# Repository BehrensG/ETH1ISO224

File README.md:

<h1>ETH1ISO224</h1>

ETH1ISO224 is a one-channel data acquisition card based on the ISO224 chip. The communication with a PC is over Ethernet. The card supports LAN eXtensions for Instrumentation (LXI) and RAW TCP and UDP connections.

> [!CAUTION]
> This design is still in verification phase. The device requires a calibration and validation to be done.

<h2>DESCRIPTION</h2>

<h3>Device Design</h3>

Key features of the design include:

<ul>
    <li><b>Dimensions</b>: 100 x 45 mm</li>
    <li><b>Power Supply</b>: Operates on a voltage range from 6.5 to 36 VDC (recommended 24 VDC) and includes reverse voltage protection.</li>
    <li><b>Isolation</b>: The ISO224 chip with TBA 1-0513HI provides isolation protection for the rest of the circuit.</li>
    <li><b>MCU</b>: The STM32H743VITx was selected because of its large internal FLASH and RAM memory, support for Ethernet, and internal 16-bit ADC.</li>
    <li><b>ADC</b>: Internal 16 bit ADC, configured in differential mode.</li>
    <li><b>Software</b>: FreeRTOS with lwip and SCPI parser library.</li>
</ul>

<p align="center">3D model rendition for PCB V1.2.</p>
<p align="center"></img></p>

<p align="center">Below are the images for the PCB V1.0.</p>

<p align="center"></img></p>
<p align="center"></img></p>
<p align="center"></img></p>

<h3>Input voltage</h3>

The PCB was designed for max bipolar 1000V DC measurements. It will divide the input voltage by 100. The user can use 1776-C68xx or SMD resistors to create the voltage divider.

> [!CAUTION]
> The PCB is still in verification. There are no guarantees that it can handle 1000 VDC safely.

<h2>Ethernet connection</h2>

The PCB uses Ethernet to communicate with the PC. The features are :

<h3>LAN eXtensions for Instrumentation (LXI)</h3>

LAN eXtensions for Instrumentation (LXI) is a standard for connecting and controlling test and measurement instruments via Ethernet. It allows for easy integration, remote access, and simplified configuration, enhancing the flexibility and scalability of automated test systems.

> [!WARNING]  
> This device does not guarantee full compliance with the LXI standard. The implementation was based on available documentation and observations of an LXI-compliant device.

> [!TIP]
> To use the LXI features the user needs to use a VISA API. In the examples below, the R&S VISA Tools where uses. 

<h4><p align="center">Device autodetect with multicast DNS (mDNS).</p></h4>
<hr>
<p align="center"></img></p>

<h4><p align="center">Support for High Speed LAN Instrument Protocol (HiSLIP).</p></h4>
<hr>
<p align="center"></img></p>

<h4><p align="center">Web interface</p></h4>
<hr>
The device website provides the ability to obtain device information, make measurements, and configure the device. Additionally, it offers a manual with all SCPI commands.

> [!WARNING]
> The website was tested only with Google Chrome  Browser.

<h5><p align="center">Device Home Page</p></h5>
<hr>
<p align="center"></img></p>

<h5><p align="center">Device Network Setup</p></h5>
<hr>
<p align="center"></img></p>

<h5><p align="center">Device Control</p></h5>
<hr>
<p align="center"></img></p>

<h5><p align="center">Device Help</p></h5>
<hr>
<p align="center"></img></p>

<h5><p align="center">Device Service</p></h5>
<hr>
<p align="center"></img></p>

<h3>RAW TCP</h3>
The user can connect to the device directly over the TCP 5025 port.

<h5><p align="center">Using netcat</p></h5>
<hr>
<p align="center"></img></p>

<h5><p align="center">Using putty</p></h5>
<hr>
<p align="center"></img></p>

<h3>RAW UDP</h3>
The user can connect to the device directly via UDP port 5025. Over UDP, there is a very limited set of SCPI commands available for measurement readout.

> [!WARNING]
> The RAW UDP connection is not part of the LXI standard, it is device specific.

<h5><p align="center">Using netcat</p></h5>
<hr>
<p align="center"></img></p>

<h2>Links</h2>

<ul>
    <li><a href="https://www.ti.com/product/ISO224" target="_blank">ISO224</a></li>
    <li><a href="https://www.lxistandard.org/" target="_blank">LAN eXtensions for Instrumentation</a></li>
    <li><a href="https://www.ivifoundation.org/specifications/default.html" target="_blank">High Speed LAN Instrument Protocol (HiSLIP)</a></li>
    <li><a href="https://en.wikipedia.org/wiki/Virtual_instrument_software_architecture" target="_blank">Virtual instrument software architecture (VISA)</a></li>
    <li><a href="https://www.rohde-schwarz.com/us/driver-pages/remote-control/3-visa-and-tools_231388.html" target="_blank">R&S VISA</a></li>
    <li><a href="https://github.com/j123b567/scpi-parser" target="_blank">SCPI Parser</a></li>
   <li><a href="https://github.com/mpaland/printf" target="_blank">A printf / sprintf Implementation for Embedded Systems</a></li>
</ul>

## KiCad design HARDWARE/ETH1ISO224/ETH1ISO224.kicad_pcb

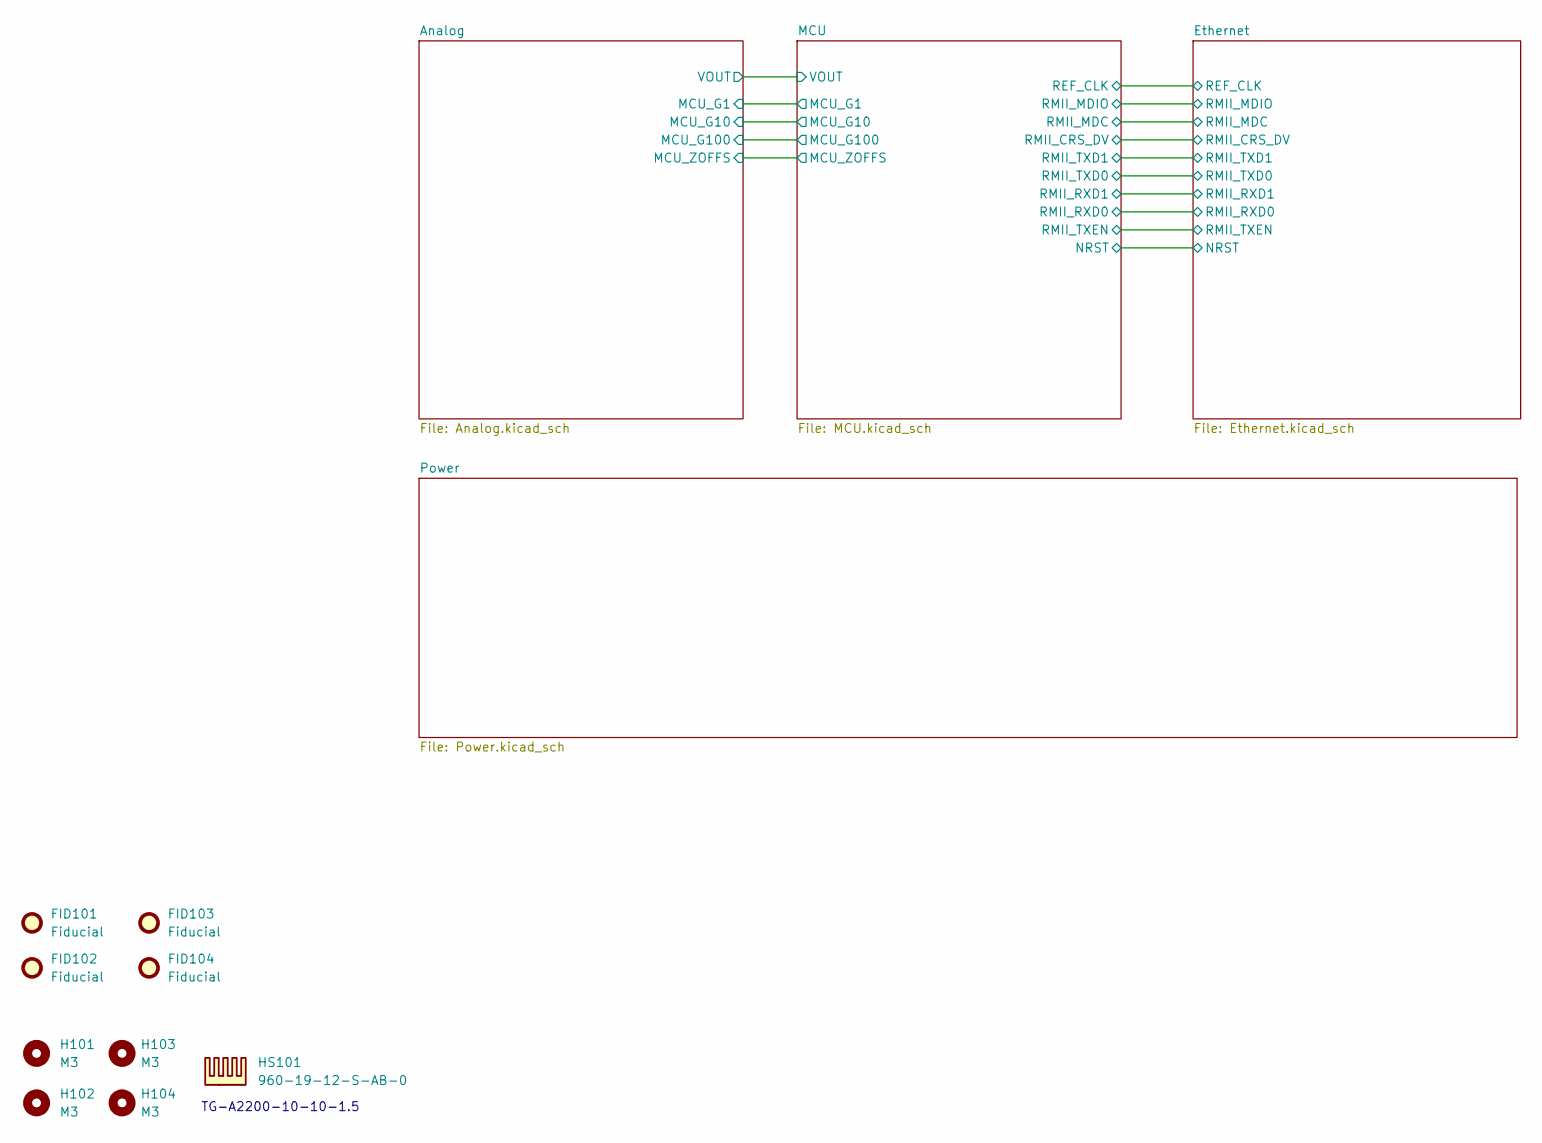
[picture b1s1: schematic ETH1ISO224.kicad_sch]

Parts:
FID101, FID102, FID103, FID104: Fiducial; Fiducial_1.5mm_Mask3mm
H101, H102: M3; MountingHole_3.2mm_M3_DIN965
H103, H104: M3; MountingHole_3.2mm_M3_DIN965_Pad
HS101: 960-19-12-S-AB-0

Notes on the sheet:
TG-A2200-10-10-1.5

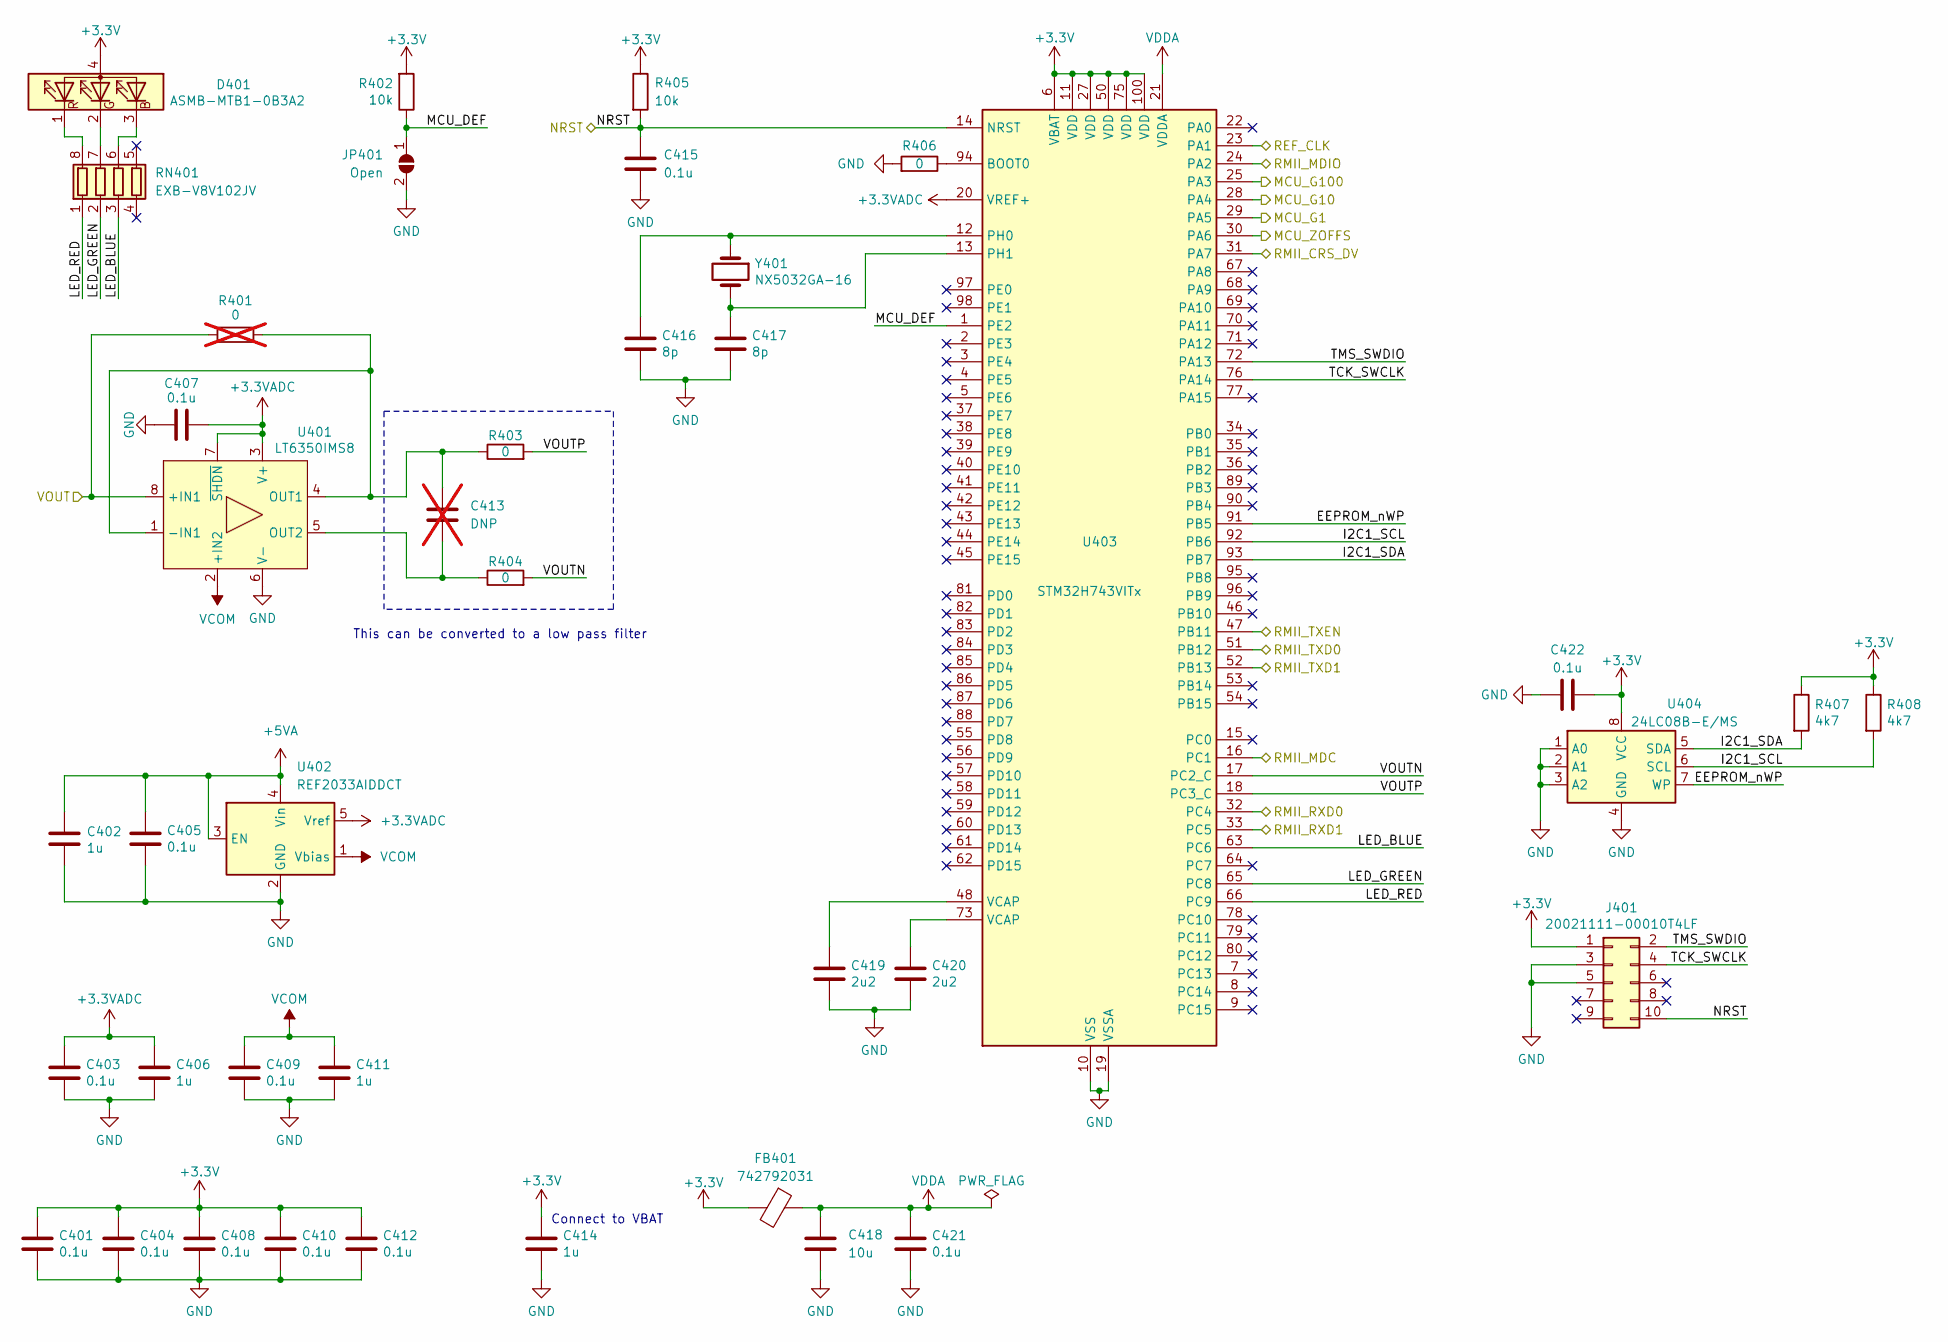
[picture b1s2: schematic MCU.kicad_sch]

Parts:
C401, C403, C404, C405, C407, C408, C409, C410, C412, C415, C421, C422: 0.1u; C_0603_1608Metric_Pad1.08x0.95mm_HandSolder
C402, C406, C411, C414: 1u; C_0603_1608Metric_Pad1.08x0.95mm_HandSolder
C413: DNP; C_0603_1608Metric_Pad1.08x0.95mm_HandSolder; not fitted
C416, C417: 8p; C_0603_1608Metric_Pad1.08x0.95mm_HandSolder
C418: 10u; C_0603_1608Metric_Pad1.08x0.95mm_HandSolder
C419, C420: 2u2; C_0603_1608Metric_Pad1.08x0.95mm_HandSolder
D401: ASMB-MTB1-0B3A2; LED_Avago_PLCC4_3.2x2.8mm_CW
FB401: 742792031; L_0805_2012Metric_Pad1.05x1.20mm_HandSolder
J401: 20021111-00010T4LF; PinHeader_2x05_P1.27mm_Vertical
JP401: Open; SolderJumper-2_P1.3mm_Open_Pad1.0x1.5mm
R401: 0; R_0603_1608Metric_Pad0.98x0.95mm_HandSolder; not fitted
R402, R405: 10k; R_0603_1608Metric_Pad0.98x0.95mm_HandSolder
R403, R404, R406: 0; R_0603_1608Metric_Pad0.98x0.95mm_HandSolder
R407, R408: 4k7; R_0603_1608Metric_Pad0.98x0.95mm_HandSolder
RN401: EXB-V8V102JV; R_Array_Concave_4x0603
U401: LT6350IMS8; MSOP-8_3x3mm_P0.65mm
U402: REF2033AIDDCT; SOT-23-5
U403: STM32H743VITx; LQFP-100_14x14mm_P0.5mm
U404: 24LC08B-E/MS; MSOP-8_3x3mm_P0.65mm
Y401: NX5032GA-16; NX5032GA

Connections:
+3.3V: C401.1, C404.1, C408.1, C410.1, C412.1, C414.1, C422.2, D401.4 (A), FB401.2, J401.1, R402.2, R405.1, R407.1, R408.1, U403.6 (VBAT), U403.11 (VDD), U403.27 (VDD), U403.50 (VDD), U403.75 (VDD), U403.100 (VDD), U404.8 (VCC); also elsewhere on the board
+3.3VADC: C403.1, C406.1, C407.1, U401.3 (V+), U401.7 (~SHDN), U402.5 (Vref), U403.20 (VREF+)
+5VA: C402.1, C405.1, U402.3 (EN), U402.4 (Vin); also elsewhere on the board
/Analog/MCU_G1: U403.29 (PA5); also elsewhere on the board
/Analog/MCU_G10: U403.28 (PA4); also elsewhere on the board
/Analog/MCU_G100: U403.25 (PA3); also elsewhere on the board
/Analog/MCU_ZOFFS: U403.30 (PA6); also elsewhere on the board
/Analog/VOUT: R401.1, U401.8 (+IN1); also elsewhere on the board
/Ethernet/REF_CLK: U403.23 (PA1); also elsewhere on the board
/Ethernet/RMII_CRS_DV: U403.31 (PA7); also elsewhere on the board
/Ethernet/RMII_MDC: U403.16 (PC1); also elsewhere on the board
/Ethernet/RMII_MDIO: U403.24 (PA2); also elsewhere on the board
/Ethernet/RMII_RXD0: U403.32 (PC4); also elsewhere on the board
/Ethernet/RMII_RXD1: U403.33 (PC5); also elsewhere on the board
/Ethernet/RMII_TXD0: U403.51 (PB12); also elsewhere on the board
/Ethernet/RMII_TXD1: U403.52 (PB13); also elsewhere on the board
/Ethernet/RMII_TXEN: U403.47 (PB11); also elsewhere on the board
/MCU/EEPROM_nWP: U403.91 (PB5), U404.7 (WP)
/MCU/I2C1_SCL: R408.2, U403.92 (PB6), U404.6 (SCL)
/MCU/I2C1_SDA: R407.2, U403.93 (PB7), U404.5 (SDA)
/MCU/LED_BLUE: RN401.3 (R3.1), U403.63 (PC6)
/MCU/LED_GREEN: RN401.2 (R2.1), U403.65 (PC8)
/MCU/LED_RED: RN401.1 (R1.1), U403.66 (PC9)
/MCU/MCU_DEF: JP401.1 (A), R402.1, U403.1 (PE2)
/MCU/NRST: C415.1, J401.10, R405.2, U403.14 (NRST); also elsewhere on the board
/MCU/TCK_SWCLK: J401.4, U403.76 (PA14)
/MCU/TMS_SWDIO: J401.2, U403.72 (PA13)
/MCU/VOUTN: R404.2, U403.17 (PC2_C)
/MCU/VOUTP: R403.2, U403.18 (PC3_C)
GND: C401.2, C402.2, C403.2, C404.2, C405.2, C406.2, C407.2, C408.2, C409.2, C410.2, C411.2, C412.2, C414.2, C415.2, C416.2, C417.2, C418.2, C419.2, C420.2, C421.2, C422.1, J401.3, J401.5, JP401.2 (B), R406.2, U401.6 (V-), U402.2 (GND), U403.10 (VSS), U403.19 (VSSA), U403.26 (VSS), U403.49 (VSS), U403.74 (VSS), U403.99 (VSS), U404.1 (A0), U404.2 (A1), U404.3 (A2), U404.4 (GND); also elsewhere on the board
unnamed: C419.1, U403.48 (VCAP)
unnamed: C420.1, U403.73 (VCAP)
unnamed: D401.3 (BK), RN401.6 (R3.2)
unnamed: D401.2 (GK), RN401.7 (R2.2)
unnamed: D401.1 (RK), RN401.8 (R1.2)
unnamed: C413.1, R401.2, R403.1, U401.1 (-IN1), U401.4 (OUT1)
unnamed: C413.2, R404.1, U401.5 (OUT2)
unnamed: R406.1, U403.94 (BOOT0)
unnamed: C416.1, U403.12 (PH0), Y401.1
unnamed: C417.1, U403.13 (PH1), Y401.2
VCOM: C409.1, C411.1, U401.2 (+IN2), U402.1 (Vbias); also elsewhere on the board
VDDA: C418.1, C421.1, FB401.1, U403.21 (VDDA)

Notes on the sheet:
This can be converted to a low pass filter
Connect to VBAT

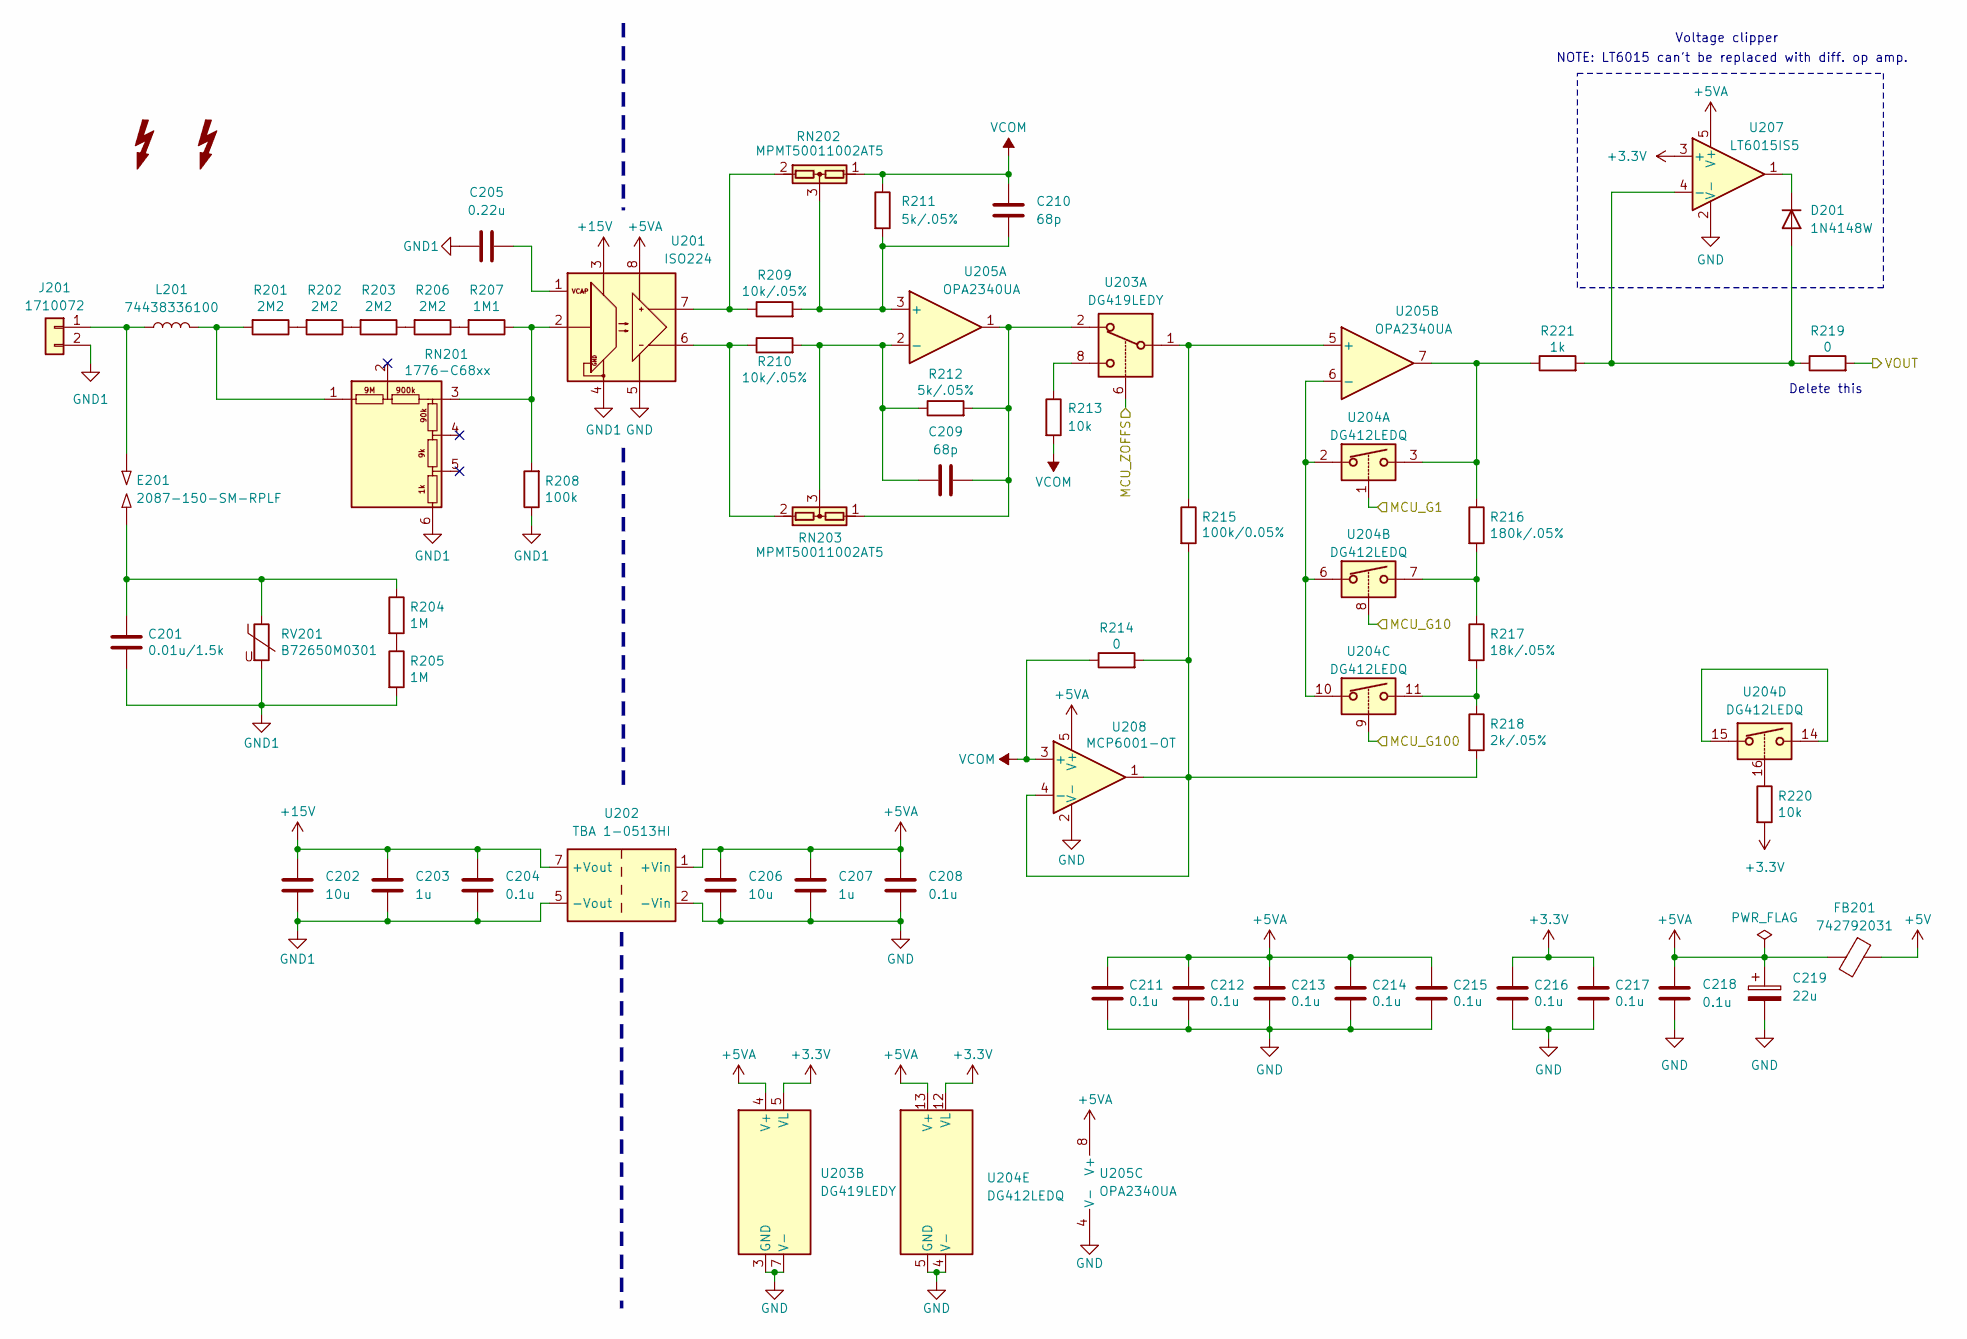
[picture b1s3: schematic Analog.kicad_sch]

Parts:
C201: 0.01u/1.5k; C_1206_3216Metric_Pad1.33x1.80mm_HandSolder
C202, C206: 10u; C_1206_3216Metric_Pad1.33x1.80mm_HandSolder
C203, C207: 1u; C_0603_1608Metric_Pad1.08x0.95mm_HandSolder
C204, C208, C211, C212, C213, C214, C215, C216, C217, C218: 0.1u; C_0603_1608Metric_Pad1.08x0.95mm_HandSolder
C205: 0.22u; C_0603_1608Metric_Pad1.08x0.95mm_HandSolder
C209, C210: 68p; C_0603_1608Metric_Pad1.08x0.95mm_HandSolder
C219: 22u; CP_EIA-3528-21_Kemet-B_Pad1.50x2.35mm_HandSolder
D201: 1N4148W; D_SOD-123
E201: 2087-150-SM-RPLF; 2087
FB201: 742792031; L_0805_2012Metric_Pad1.05x1.20mm_HandSolder
J201: 1710072
L201: 74438336100; L_Wuerth_MAPI-3015
R201, R202, R203, R206: 2M2; R_1206_3216Metric_Pad1.30x1.75mm_HandSolder
R204, R205: 1M; R_1206_3216Metric_Pad1.30x1.75mm_HandSolder
R207: 1M1; R_1206_3216Metric_Pad1.30x1.75mm_HandSolder
R208: 100k; R_1206_3216Metric_Pad1.30x1.75mm_HandSolder
R209, R210: 10k/.05%; R_0603_1608Metric_Pad0.98x0.95mm_HandSolder
R211, R212: 5k/.05%; R_0603_1608Metric_Pad0.98x0.95mm_HandSolder
R213, R220: 10k; R_0603_1608Metric_Pad0.98x0.95mm_HandSolder
R214, R219: 0; R_0603_1608Metric_Pad0.98x0.95mm_HandSolder
R215: 100k/0.05%; R_0603_1608Metric_Pad0.98x0.95mm_HandSolder
R216: 180k/.05%; R_0603_1608Metric_Pad0.98x0.95mm_HandSolder
R217: 18k/.05%; R_0603_1608Metric_Pad0.98x0.95mm_HandSolder
R218: 2k/.05%; R_0603_1608Metric_Pad0.98x0.95mm_HandSolder
R221: 1k; R_0603_1608Metric_Pad0.98x0.95mm_HandSolder
RN201: 1776-C68xx
RN202, RN203: MPMT50011002AT5; SOT-23
RV201: B72650M0301; Varistor_Panasonic_VF
SYM201, SYM202: SYM_Flash_Small; Symbol_Attention_Triangle_8x7mm_Copper
U201: ISO224; SSO-8_6.8x5.9mm_P1.27mm_Clearance8mm
U202: TBA 1-0513HI; TBA 1HI
U203: DG419LEDY; SOIC-8_3.9x4.9mm_P1.27mm
U204: DG412LEDQ; TSSOP-16_4.4x5mm_P0.65mm
U205: OPA2340UA; SOIC-8_3.9x4.9mm_P1.27mm
U207: LT6015IS5; SOT-23-5
U208: MCP6001-OT; SOT-23-5

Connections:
+3.3V: C216.1, C217.1, R220.2, U203.5 (VL), U204.12 (VL), U207.3 (+); also elsewhere on the board
+5V: FB201.1; also elsewhere on the board
+5VA: C206.1, C207.1, C208.1, C211.1, C212.1, C213.1, C214.1, C215.1, C218.1, C219.1, FB201.2, U201.8 (VDD2), U202.1 (+Vin), U203.4 (V+), U204.13 (V+), U205.8 (V+), U207.5 (V+), U208.5 (V+); also elsewhere on the board
+15V: C202.1, C203.1, C204.1, U201.3 (VDD1), U202.7 (+Vout)
/Analog/MCU_G1: U204.1; also elsewhere on the board
/Analog/MCU_G10: U204.8; also elsewhere on the board
/Analog/MCU_G100: U204.9; also elsewhere on the board
/Analog/MCU_ZOFFS: U203.6; also elsewhere on the board
/Analog/VOUT: R219.2; also elsewhere on the board
GND: C206.2, C207.2, C208.2, C211.2, C212.2, C213.2, C214.2, C215.2, C216.2, C217.2, C218.2, C219.2, U201.5 (GND2), U202.2 (-Vin), U203.3 (GND), U203.7 (V-), U204.4 (V-), U204.5 (GND), U205.4 (V-), U207.2 (V-), U208.2 (V-); also elsewhere on the board
GND1: C201.2, C202.2, C203.2, C204.2, C205.1, J201.2, R205.2, R208.1, RN201.6 (R5), RV201.2, U201.4 (GND1), U202.5 (-Vout)
unnamed: C201.1, E201.1, R204.1, RV201.1
unnamed: C209.2, R212.2, RN203.1, U203.2, U205.1
unnamed: D201.2 (A), R219.1, R221.2, U207.4 (-)
unnamed: D201.1 (K), U207.1
unnamed: E201.2, J201.1, L201.1
unnamed: R201.1, R202.2
unnamed: R202.1, R203.2
unnamed: R203.1, R206.2
unnamed: R204.2, R205.1
unnamed: R206.1, R207.2
unnamed: R213.1, U203.8
unnamed: R216.1, R221.1, U204.3, U205.7
unnamed: R216.2, R217.1, U204.7
unnamed: R217.2, R218.1, U204.11
unnamed: R220.1, U204.16
unnamed: R207.1, R208.2, RN201.3 (R2), U201.2 (IN)
unnamed: L201.2, R201.2, RN201.1 (common)
unnamed: R209.1, RN202.2, U201.7 (OUT+)
unnamed: R210.1, RN203.2, U201.6 (OUT-)
unnamed: C205.2, U201.1 (VCP)
unnamed: U204.14, U204.15
unnamed: C210.1, R209.2, R211.2, RN202.3, U205.3 (+)
unnamed: C209.1, R210.2, R212.1, RN203.3, U205.2 (-)
unnamed: R215.1, U203.1, U205.5 (+)
unnamed: U204.2, U204.6, U204.10, U205.6 (-)
unnamed: R214.2, R215.2, R218.2, U208.1, U208.4 (-)
VCOM: C210.2, R211.1, R213.2, R214.1, RN202.1, U208.3 (+); also elsewhere on the board

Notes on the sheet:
Voltage clipper
Delete this
NOTE: LT6015 can't be replaced with diff. op amp.

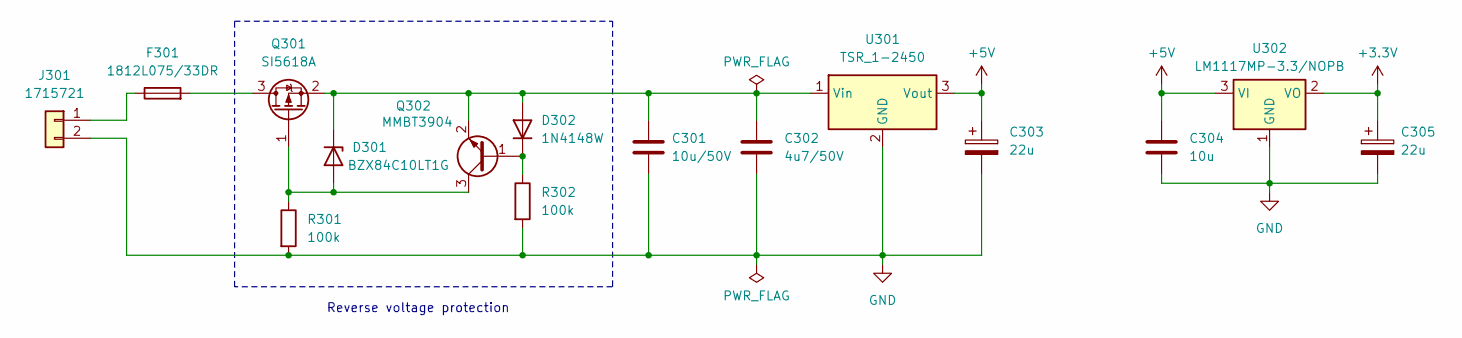
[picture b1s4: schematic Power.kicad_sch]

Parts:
C301: 10u/50V; C_1206_3216Metric_Pad1.33x1.80mm_HandSolder
C302: 4u7/50V; C_1206_3216Metric_Pad1.33x1.80mm_HandSolder
C303, C305: 22u; CP_EIA-3528-21_Kemet-B_Pad1.50x2.35mm_HandSolder
C304: 10u; C_1206_3216Metric_Pad1.33x1.80mm_HandSolder
D301: BZX84C10LT1G; SOT-23
D302: 1N4148W; D_SOD-123
F301: 1812L075/33DR; Fuse_1812_4532Metric_Pad1.30x3.40mm_HandSolder
J301: 1715721; TerminalBlock_Phoenix_MKDS-1,5-2_1x02_P5.00mm_Horizontal
Q301: SI5618A; SOT-23
Q302: MMBT3904; SOT-23
R301, R302: 100k; R_0603_1608Metric_Pad0.98x0.95mm_HandSolder
U301: TSR_1-2450; Converter_DCDC_TRACO_TSR-1_THT
U302: LM1117MP-3.3/NOPB; SOT-223-3_TabPin2

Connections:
+3.3V: C305.1, U302.2 (VO); also elsewhere on the board
+5V: C303.1, C304.1, U301.3 (Vout), U302.3 (VI); also elsewhere on the board
GND: C301.2, C302.2, C303.2, C304.2, C305.2, J301.2, R301.2, R302.2, U301.2 (GND), U302.1 (GND); also elsewhere on the board
unnamed: D301.1 (A), Q301.1 (G), Q302.3 (C), R301.1
unnamed: C301.1, C302.1, D301.3 (K), D302.2 (A), Q301.2 (S), Q302.2 (E), U301.1 (Vin)
unnamed: D302.1 (K), Q302.1 (B), R302.1
unnamed: F301.1, J301.1
unnamed: F301.2, Q301.3 (D)

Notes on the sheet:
Reverse voltage protection

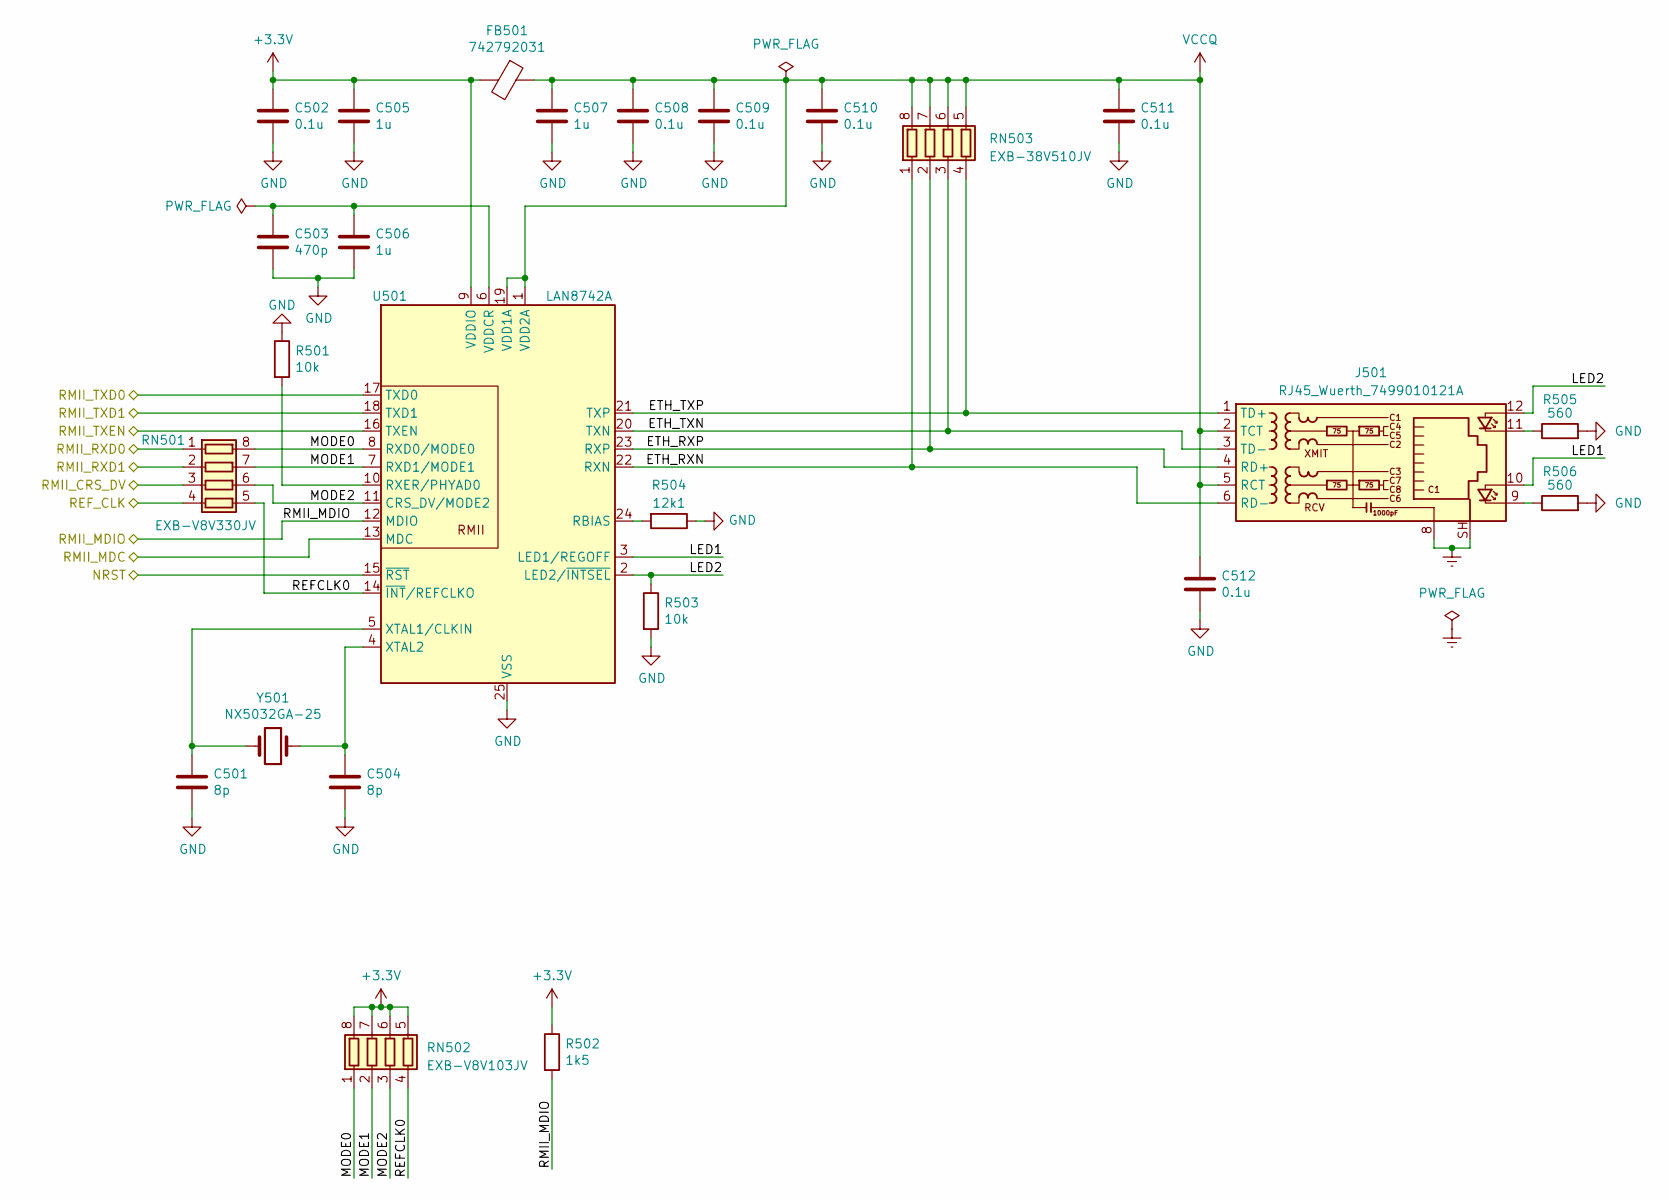
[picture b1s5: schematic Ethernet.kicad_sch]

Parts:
C501, C504: 8p; C_0603_1608Metric_Pad1.08x0.95mm_HandSolder
C502, C508, C509, C510, C511, C512: 0.1u; C_0603_1608Metric_Pad1.08x0.95mm_HandSolder
C503: 470p; C_0603_1608Metric_Pad1.08x0.95mm_HandSolder
C505, C506, C507: 1u; C_0603_1608Metric_Pad1.08x0.95mm_HandSolder
FB501: 742792031; L_0805_2012Metric_Pad1.05x1.20mm_HandSolder
J501: RJ45_Wuerth_7499010121A; RJ45_Wuerth_7499010121A_Horizontal
R501, R503: 10k; R_0603_1608Metric_Pad0.98x0.95mm_HandSolder
R502: 1k5; R_0603_1608Metric_Pad0.98x0.95mm_HandSolder
R504: 12k1; R_0603_1608Metric_Pad0.98x0.95mm_HandSolder
R505, R506: 560; R_0603_1608Metric_Pad0.98x0.95mm_HandSolder
RN501: EXB-V8V330JV; R_Array_Concave_4x0603
RN502: EXB-V8V103JV; R_Array_Concave_4x0603
RN503: EXB-38V510JV; R_Array_Concave_4x0603
U501: LAN8742A; VQFN-24-1EP_4x4mm_P0.5mm_EP2.5x2.5mm_ThermalVias
Y501: NX5032GA-25; NX5032GA

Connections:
+3.3V: C502.1, C505.1, FB501.2, R502.1, RN502.5 (R4.2), RN502.6 (R3.2), RN502.7 (R2.2), RN502.8 (R1.2), U501.9 (VDDIO); also elsewhere on the board
/Ethernet/ETH_RXN: J501.6 (RD-), RN503.1 (R1.1), U501.22 (RXN)
/Ethernet/ETH_RXP: J501.4 (RD+), RN503.2 (R2.1), U501.23 (RXP)
/Ethernet/ETH_TXN: J501.3 (TD-), RN503.3 (R3.1), U501.20 (TXN)
/Ethernet/ETH_TXP: J501.1 (TD+), RN503.4 (R4.1), U501.21 (TXP)
/Ethernet/LED1: J501.10, U501.3 (LED1/REGOFF)
/Ethernet/LED2: J501.12, R503.1, U501.2 (LED2/~INTSEL)
/Ethernet/MODE0: RN501.8 (R1.2), RN502.1 (R1.1), U501.8 (RXD0/MODE0)
/Ethernet/MODE1: RN501.7 (R2.2), RN502.2 (R2.1), U501.7 (RXD1/MODE1)
/Ethernet/MODE2: RN501.6 (R3.2), RN502.3 (R3.1), U501.11 (CRS_DV/MODE2)
/Ethernet/REFCLK0: RN501.5 (R4.2), RN502.4 (R4.1), U501.14 (~INT/REFCLKO)
/Ethernet/REF_CLK: RN501.4 (R4.1); also elsewhere on the board
/Ethernet/RMII_CRS_DV: RN501.3 (R3.1); also elsewhere on the board
/Ethernet/RMII_MDC: U501.13 (MDC); also elsewhere on the board
/Ethernet/RMII_MDIO: R502.2, U501.12 (MDIO); also elsewhere on the board
/Ethernet/RMII_RXD0: RN501.1 (R1.1); also elsewhere on the board
/Ethernet/RMII_RXD1: RN501.2 (R2.1); also elsewhere on the board
/Ethernet/RMII_TXD0: U501.17 (TXD0); also elsewhere on the board
/Ethernet/RMII_TXD1: U501.18 (TXD1); also elsewhere on the board
/Ethernet/RMII_TXEN: U501.16 (TXEN); also elsewhere on the board
/MCU/NRST: U501.15 (~RST); also elsewhere on the board
Earth: J501.8, J501.SH
GND: C501.2, C502.2, C503.2, C504.2, C505.2, C506.2, C507.2, C508.2, C509.2, C510.2, C511.2, C512.2, R501.1, R503.2, R504.1, R505.2, R506.2, U501.25 (VSS); also elsewhere on the board
unnamed: J501.9, R506.1
unnamed: J501.11, R505.1
unnamed: R504.2, U501.24 (RBIAS)
unnamed: R501.2, U501.10 (RXER/PHYAD0)
unnamed: C503.1, C506.1, U501.6 (VDDCR)
unnamed: C501.1, U501.5 (XTAL1/CLKIN), Y501.2
unnamed: C504.1, U501.4 (XTAL2), Y501.1
VCCQ: C507.1, C508.1, C509.1, C510.1, C511.1, C512.1, FB501.1, J501.2 (TCT), J501.5 (RCT), RN503.5 (R4.2), RN503.6 (R3.2), RN503.7 (R2.2), RN503.8 (R1.2), U501.1 (VDD2A), U501.19 (VDD1A)

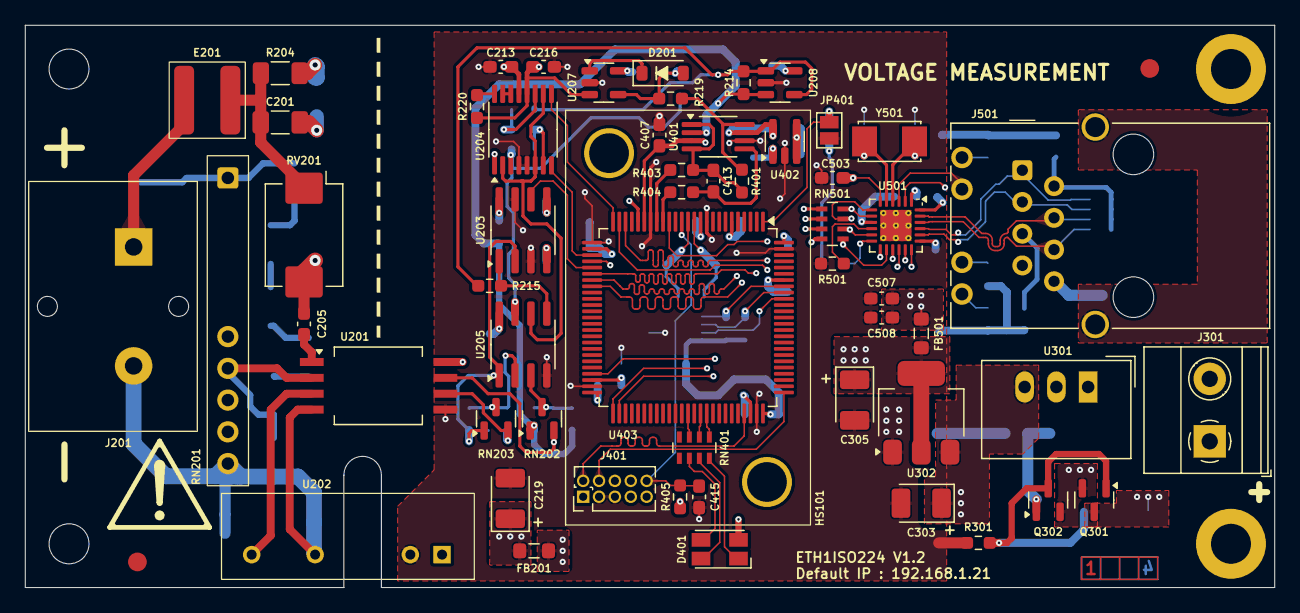
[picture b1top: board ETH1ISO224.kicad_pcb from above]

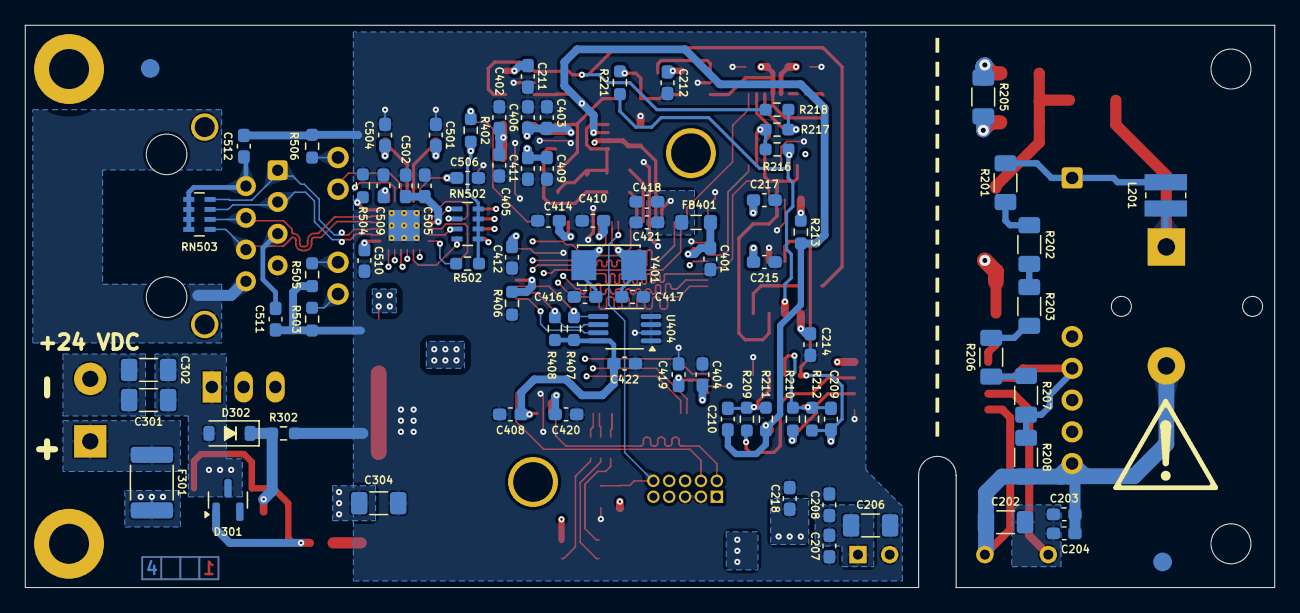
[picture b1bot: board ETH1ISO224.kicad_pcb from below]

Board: 4 copper layers, 100.0 x 45.0 mm, 147 parts (83 on the bottom side), 95 nets.

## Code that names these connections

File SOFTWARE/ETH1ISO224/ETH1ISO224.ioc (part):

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Mcu.Name=STM32H743VITx
Mcu.Package=LQFP100
Mcu.UserName=STM32H743VITx
PA1.GPIOParameters=GPIO_Speed
PA1.GPIO_Speed=GPIO_SPEED_FREQ_VERY_HIGH
PA1.Mode=RMII
PA1.Signal=ETH_REF_CLK
PA2.GPIOParameters=GPIO_Speed
PA2.GPIO_Speed=GPIO_SPEED_FREQ_VERY_HIGH
PA2.Mode=RMII
PA2.Signal=ETH_MDIO
PA3.GPIOParameters=PinState,GPIO_Label
PA3.GPIO_Label=MCU_G100
PA3.PinState=GPIO_PIN_RESET
PA3.Signal=GPIO_Output
PA4.GPIOParameters=GPIO_Speed,PinState,GPIO_Label
PA4.GPIO_Label=MCU_G10
PA4.GPIO_Speed=GPIO_SPEED_FREQ_HIGH
PA4.PinState=GPIO_PIN_RESET
PA4.Signal=GPIO_Output
PA5.GPIOParameters=GPIO_Speed,PinState,GPIO_Label
PA5.GPIO_Label=MCU_G1
PA5.GPIO_Speed=GPIO_SPEED_FREQ_HIGH
PA5.PinState=GPIO_PIN_SET
PA5.Signal=GPIO_Output
PA6.GPIOParameters=GPIO_Label
PA6.GPIO_Label=MCU_ZOFFS
PA6.Signal=GPIO_Output
PA7.GPIOParameters=GPIO_Speed
PA7.GPIO_Speed=GPIO_SPEED_FREQ_VERY_HIGH
PA7.Mode=RMII
PA7.Signal=ETH_CRS_DV
PB11.GPIOParameters=GPIO_Speed
PB11.GPIO_Speed=GPIO_SPEED_FREQ_VERY_HIGH
PB11.Mode=RMII
PB11.Signal=ETH_TX_EN
PB12.GPIOParameters=GPIO_Speed
PB12.GPIO_Speed=GPIO_SPEED_FREQ_VERY_HIGH
PB12.Mode=RMII
PB12.Signal=ETH_TXD0
PB13.GPIOParameters=GPIO_Speed
PB13.GPIO_Speed=GPIO_SPEED_FREQ_VERY_HIGH
PB13.Mode=RMII
PB13.Signal=ETH_TXD1
PB5.GPIOParameters=GPIO_Speed,PinState,GPIO_Label
PB5.GPIO_Label=EEPROM_nWP
PB5.GPIO_Speed=GPIO_SPEED_FREQ_HIGH
PB5.PinState=GPIO_PIN_SET
PB5.Signal=GPIO_Output
PB6.Mode=I2C
PB6.Signal=I2C1_SCL
PB7.Mode=I2C
PB7.Signal=I2C1_SDA
PC1.GPIOParameters=GPIO_Speed
PC1.GPIO_Speed=GPIO_SPEED_FREQ_LOW
PC1.Mode=RMII
PC1.Signal=ETH_MDC
PC2_C.Mode=IN1-Differential
PC2_C.Signal=ADC3_INN1
PC3_C.Mode=IN1-Differential
PC3_C.Signal=ADC3_INP1
PC4.GPIOParameters=GPIO_Speed
PC4.GPIO_Speed=GPIO_SPEED_FREQ_VERY_HIGH
PC4.Mode=RMII
PC4.Signal=ETH_RXD0
PC5.GPIOParameters=GPIO_Speed
PC5.GPIO_Speed=GPIO_SPEED_FREQ_VERY_HIGH
PC5.Mode=RMII
PC5.Signal=ETH_RXD1
PC6.GPIOParameters=PinState,GPIO_Label
PC6.GPIO_Label=LED_BLUE
PC6.PinState=GPIO_PIN_SET
PC6.Signal=GPIO_Output
PC8.GPIOParameters=PinState,GPIO_Label
PC8.GPIO_Label=LED_GREEN
PC8.PinState=GPIO_PIN_SET
PC8.Signal=GPIO_Output
PC9.GPIOParameters=PinState,GPIO_Label
PC9.GPIO_Label=LED_RED
PC9.PinState=GPIO_PIN_SET
PC9.Signal=GPIO_Output
PE2.GPIOParameters=GPIO_Label
PE2.GPIO_Label=MCU_DEFAULT
PE2.Signal=GPIO_Input
PH0-OSC_IN\ (PH0).Mode=HSE-External-Oscillator
PH0-OSC_IN\ (PH0).Signal=RCC_OSC_IN
PH1-OSC_OUT\ (PH1).Mode=HSE-External-Oscillator
PH1-OSC_OUT\ (PH1).Signal=RCC_OSC_OUT
RCC.HSE_VALUE=16000000
RCC.SYSCLKFreq_VALUE=480000000
RCC.SYSCLKSource=RCC_SYSCLKSOURCE_PLLCLK
board=custom

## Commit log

2024-04-26 Hardware design
2024-04-28 Hardware design done
2024-04-28 Footprint change, not critical
2024-05-04 Changed REF19 to REF20
2024-05-06 Hardware changes
2024-05-08 Software development
2024-05-12 PCB changes
2024-05-14 IOC file configuration and code generation.
2024-05-19 Fixes in null offset
2024-05-19 Bug fix
2024-05-21 Added new SCPI commands. Bug fixes.
2024-05-21 UDP speed improvement.
2024-05-22 Added TIM3 timer for LED status blink. Changes in SCPI commands.
2024-05-23 Changes in SCPI commands.
2024-05-23 Bug fixes
2024-05-31 Changed LWIP TCP parameres for better TCP performace.
2024-07-02 Software update : HiSLIP, HTTP, RAW TCP
2024-07-06 README.md
2024-07-06 Changed web_Control.png
2024-07-18 Bug fixes.
2024-08-30 New features.
